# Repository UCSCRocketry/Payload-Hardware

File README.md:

# Payload-Hardware
UCSC Rocketry's Deployed Payload Hardware System

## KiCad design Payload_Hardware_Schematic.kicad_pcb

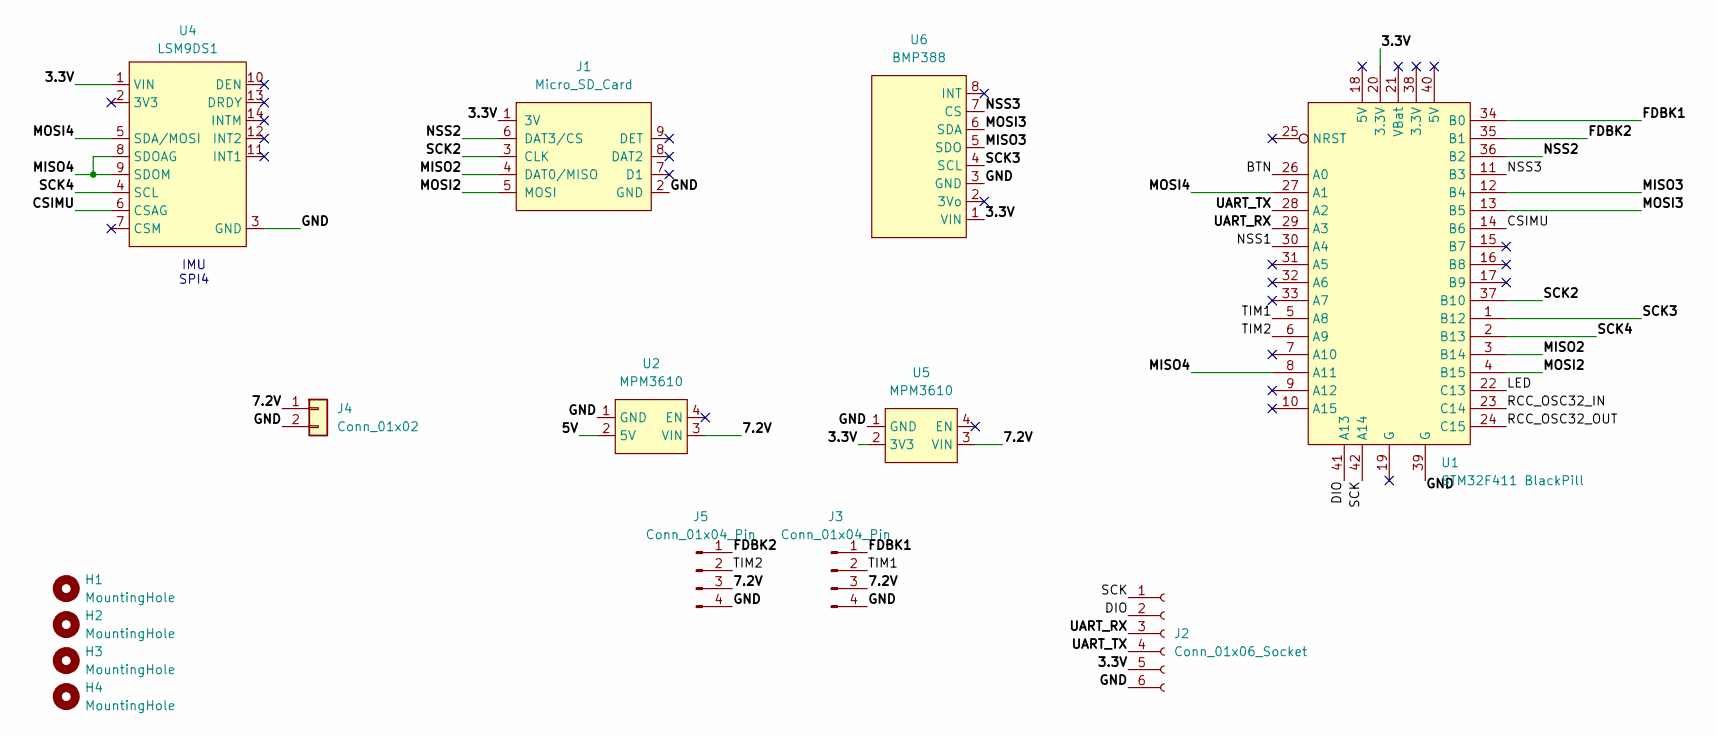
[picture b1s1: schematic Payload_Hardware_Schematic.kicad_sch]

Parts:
H1, H2, H3, H4: MountingHole; MountingHole_3.2mm_M3_DIN965_Pad
J1: Micro_SD_Card; Micro_SD
J2: Conn_01x06_Socket; PinSocket_1x06_P2.54mm_Horizontal
J3, J5: Conn_01x04_Pin; PinHeader_1x04_P2.54mm_Horizontal
J4: Conn_01x02; CONN_SD-43650-001_02_MOL
U1: STM32F411 BlackPill; STM32F411_Black_Pill
U2, U5: MPM3610
U4: LSM9DS1
U6: BMP388; BMP388_Breakout

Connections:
/5V: U2.2 (5V)
/7.2V: J3.3, J4.1, J5.3, U2.3 (VIN), U5.3 (VIN)
/<NO NET>: J1.1 (3V), J2.5, U1.20 (3.3V), U4.1 (VIN), U5.2 (3V3), U6.1 (VIN)
/BTN: U1.26 (A0)
/CSIMU: U1.14 (B6), U4.6 (CSAG)
/DIO: J2.2, U1.41 (A13)
/FDBK1: J3.1, U1.34 (B0)
/FDBK2: J5.1, U1.35 (B1)
/GND: J1.2 (GND), J2.6, J3.4, J4.2, J5.4, U1.39 (G), U2.1 (GND), U4.3 (GND), U5.1 (GND), U6.3 (GND)
/LED: U1.22 (C13)
/MISO2: J1.4 (DAT0/MISO), U1.3 (B14)
/MISO3: U1.12 (B4), U6.5 (SDO)
/MISO4: U1.8 (A11), U4.8 (SDOAG), U4.9 (SDOM)
/MOSI2: J1.5 (MOSI), U1.4 (B15)
/MOSI3: U1.13 (B5), U6.6 (SDA)
/MOSI4: U1.27 (A1), U4.5 (SDA/MOSI)
/NSS1: U1.30 (A4)
/NSS2: J1.6 (DAT3/CS), U1.36 (B2)
/NSS3: U1.11 (B3), U6.7 (CS)
/RCC_OSC32_IN: U1.23 (C14)
/RCC_OSC32_OUT: U1.24 (C15)
/SCK: J2.1, U1.42 (A14)
/SCK2: J1.3 (CLK), U1.37 (B10)
/SCK3: U1.1 (B12), U6.4 (SCL)
/SCK4: U1.2 (B13), U4.4 (SCL)
/TIM1: J3.2, U1.5 (A8)
/TIM2: J5.2, U1.6 (A9)
/UART_RX: J2.3, U1.29 (A3)
/UART_TX: J2.4, U1.28 (A2)

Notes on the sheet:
IMU SPI4

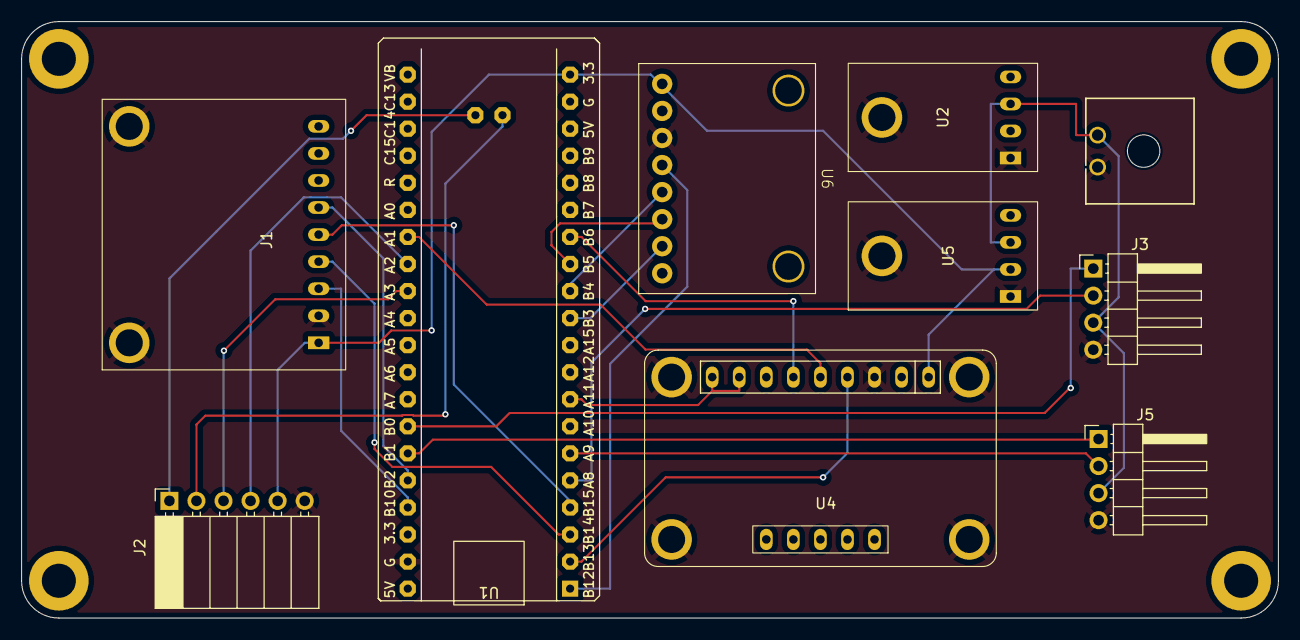
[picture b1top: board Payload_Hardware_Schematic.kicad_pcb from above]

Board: 2 copper layers, 118.0 x 56.0 mm, 14 parts (0 on the bottom side), 23 nets.

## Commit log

2026-02-10 added initial files
2026-02-10 extracted MCU footprint
2026-02-10 closed project
2026-02-10 added MCU schematic
2026-02-10 added pretty file for mcu
2026-02-10 test
2026-02-17 added avionics library
2026-02-17 SPI pins on MCU llabeled
2026-02-17 Add BMP-388 breakout footprint
2026-02-17 first commit to branch
2026-02-17 Add BMP388 breakout footprint
2026-03-03 MCU Labels
2026-03-03 3v3 and 5v buck converters added
2026-03-03 Added BMP388 Breakout Footprint and Symbol
2026-03-03 Modified BMP388 Breakout Symbol
2026-03-03 buck converters added
2026-03-03 All SPI Labeled(waiting for Altimeter dual com protocol)
2026-03-09 added pins
2026-03-12 updating full schematic
2026-03-25 copied mcu+sensors schematic and editted SD card reader schematic to match footprint
2026-03-25 removed extra file
2026-03-31 Combined Power and Electronics Schematic
2026-03-31 Added the power regulator footprints to Footprints folder
2026-04-03 Editted power and labels
2026-04-04 Fixed footprints and schematics
2026-04-06 Updated from main
2026-04-06 updated footprints
2026-04-06 fixed errors and schematic updates
2026-04-11 PCB routing-1
2026-04-13 routing
2026-04-13 Updated files to main
2026-04-13 pcb routing -1
2026-04-14 updated pins
2026-04-14 updated pins-2
2026-04-18 servo pins
2026-04-18 added DIO SCK
2026-04-21 PCB layout
2026-04-21 PCB Layout 2
2026-04-21 initial
2026-04-25 auto wiring
2026-04-27 Fixed some autorouting
2026-04-29 finalized board, changed Vbat to 3.3V
2026-04-29 Switched sd card and uart/serial access
2026-05-07 Niv's edits, moved pins close to edge and connected servos to 7.2V
2026-05-07 final gerber files
2026-05-07 gerber
